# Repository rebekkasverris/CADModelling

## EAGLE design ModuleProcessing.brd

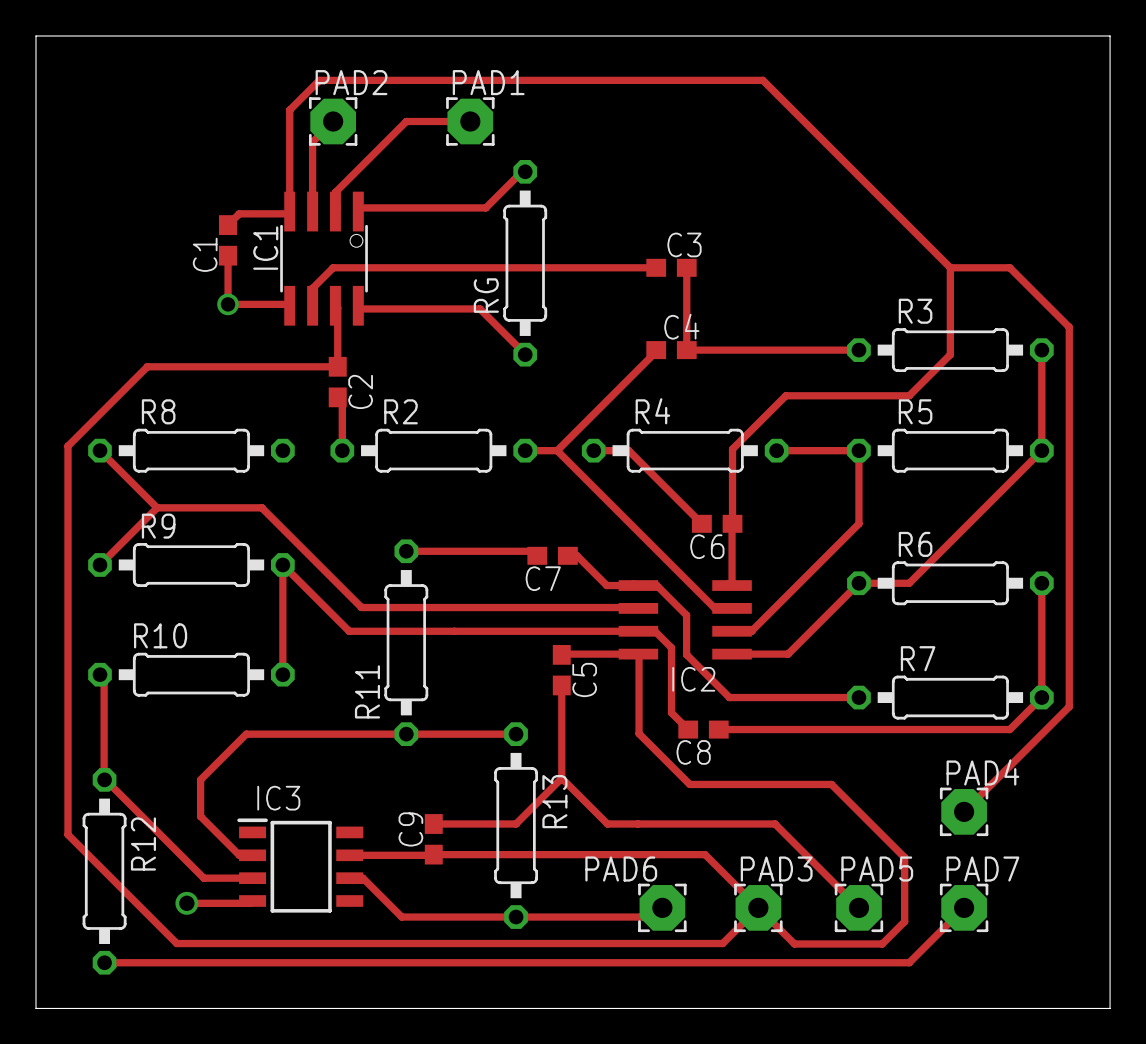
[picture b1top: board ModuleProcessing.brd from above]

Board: 2 copper layers, 59.7 x 54.0 mm, 32 parts (0 on the bottom side), 20 nets.

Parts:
C1, C2, C3, C4, C5, C6, C7, C8, C9: C0603
IC1: INA128U; SO08
IC2: LM358MX; SO08
IC3: MCP606-I_SN; SOIC127P600X175-8N
PAD1, PAD2, PAD3, PAD4, PAD5, PAD6, PAD7: WIREPAD2,54/1,1; 2,54/1,1
R2, R3, R4, R5, R6, R7, R8, R9, R10, R11, R12, R13: 0207/10
RG: 0207/10

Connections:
AGND: C1.2, C2.2, C5.2, C6.2, C7.2, C9.2, IC1.5, IC3.4, PAD5.1, R2.1, R4.1, R8.2, R11.1
ELEC1: IC1.2, PAD1.1
ELEC2: IC1.3, PAD2.1
unnamed: IC1.1, RG.2
unnamed: IC1.8, RG.1
unnamed: IC2.2, R4.2, R5.2
unnamed: IC2.1, R3.1, R5.1, R6.2
unnamed: C4.1, IC2.3, R2.2
unnamed: C3.1, C4.2, R3.2
unnamed: C3.2, IC1.6
unnamed: C8.1, R6.1, R7.2
unnamed: C7.1, IC2.5, R7.1
unnamed: C8.2, IC2.7, R9.2, R10.1
unnamed: IC2.6, R8.1, R9.1
unnamed: IC3.3, R10.2, R12.2
unnamed: IC3.2, R11.2, R13.1
SIGOUT: IC3.6, PAD6.1, R13.2
VDD: C2.1, C5.1, C9.1, IC1.7, IC2.8, IC3.7, PAD3.1
VREF: PAD7.1, R12.1
VSS: C1.1, C6.1, IC1.4, IC2.4, PAD4.1

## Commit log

2018-09-27 First schematic file created
2018-10-12 Finished pre-prototype of processing module
2018-10-14 Added bypass capacitors on Processing Module
2018-11-04 Changed board for testing before final prototype
2018-11-19 Final version of processing pre-prototype
2018-11-19 added Electrode box design
2018-11-28 drawing control module
